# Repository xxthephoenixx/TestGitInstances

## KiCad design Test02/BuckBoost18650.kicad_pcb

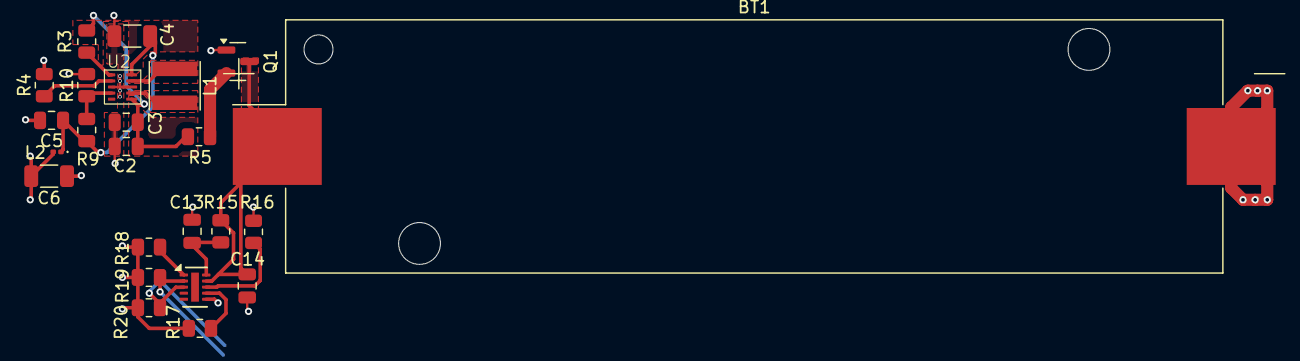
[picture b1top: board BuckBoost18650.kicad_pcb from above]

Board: 4 copper layers, 24 parts (0 on the bottom side), 18 nets.

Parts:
BT1: Battery_Cell; BatteryHolder_Keystone_1042_1x18650
C2: 10µF; C_0805_2012Metric
C3, C5: 100n; C_0805_2012Metric
C4, C6: 47µF; C_1206_3216Metric
C13: 220nF; C_0805_2012Metric
C14: 1µF; C_0805_2012Metric
L1: 470nH; L_Taiyo-Yuden_MD-4040
L2: 470nH; D_0201_0603Metric
Q1: IRLML6402; SOT-23
R3, R4, R5: 0R; R_0805_2012Metric
R9: 511k; R_0805_2012Metric
R10: 100k; R_0805_2012Metric
R15, R16: 1k; R_0805_2012Metric
R17, R18, R19, R20: 10k; R_0805_2012Metric
STC3115AIQT1: DFN-10-1EP_2x3mm_P0.5mm_EP0.64x2.4mm
U2: TPS63802DLAR; DLA0010A

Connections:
+3.3V: C6.1, L2.2
+3V3: R17.1, R18.1, R19.1, R20.1
+BATT: BT1.1 (+), C14.1, Q1.3 (D), R15.1, STC3115AIQT1.9 (VCC)
/ALM_BAT: R18.2, STC3115AIQT1.1 (ALM)
/SCL_BAT: R20.2, STC3115AIQT1.3 (SCL)
/SDA_BAT: R19.2, STC3115AIQT1.2 (SDA)
GND: BT1.2 (-), C2.2, C3.2, C4.2, C5.2, C6.2, C13.2, C14.2, Q1.1 (G), R4.2, R10.2, R16.1, STC3115AIQT1.5 (GND), STC3115AIQT1.6 (CG), U2.3 (AGND), U2.8 (GND)
unnamed: Q1.2 (S), R5.2
unnamed: R16.2, STC3115AIQT1.8 (BATD/CD)
unnamed: R17.2, STC3115AIQT1.7 (RSTIO)
unnamed: C13.1, R15.2, STC3115AIQT1.10 (VIN)
unnamed: R3.2, U2.1 (EN)
unnamed: R9.2, R10.1, U2.4 (FB)
unnamed: L1.1, U2.9 (L1)
unnamed: L1.2, U2.7 (L2)
unnamed: R4.1, U2.2 (MODE)
unnamed: C4.1, C5.1, L2.1, R9.1, U2.6 (VOUT)
V_Supply: C2.1, C3.1, R3.1, R5.1, U2.10 (VIN)

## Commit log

2025-05-13 init
2025-05-13 .
    .
